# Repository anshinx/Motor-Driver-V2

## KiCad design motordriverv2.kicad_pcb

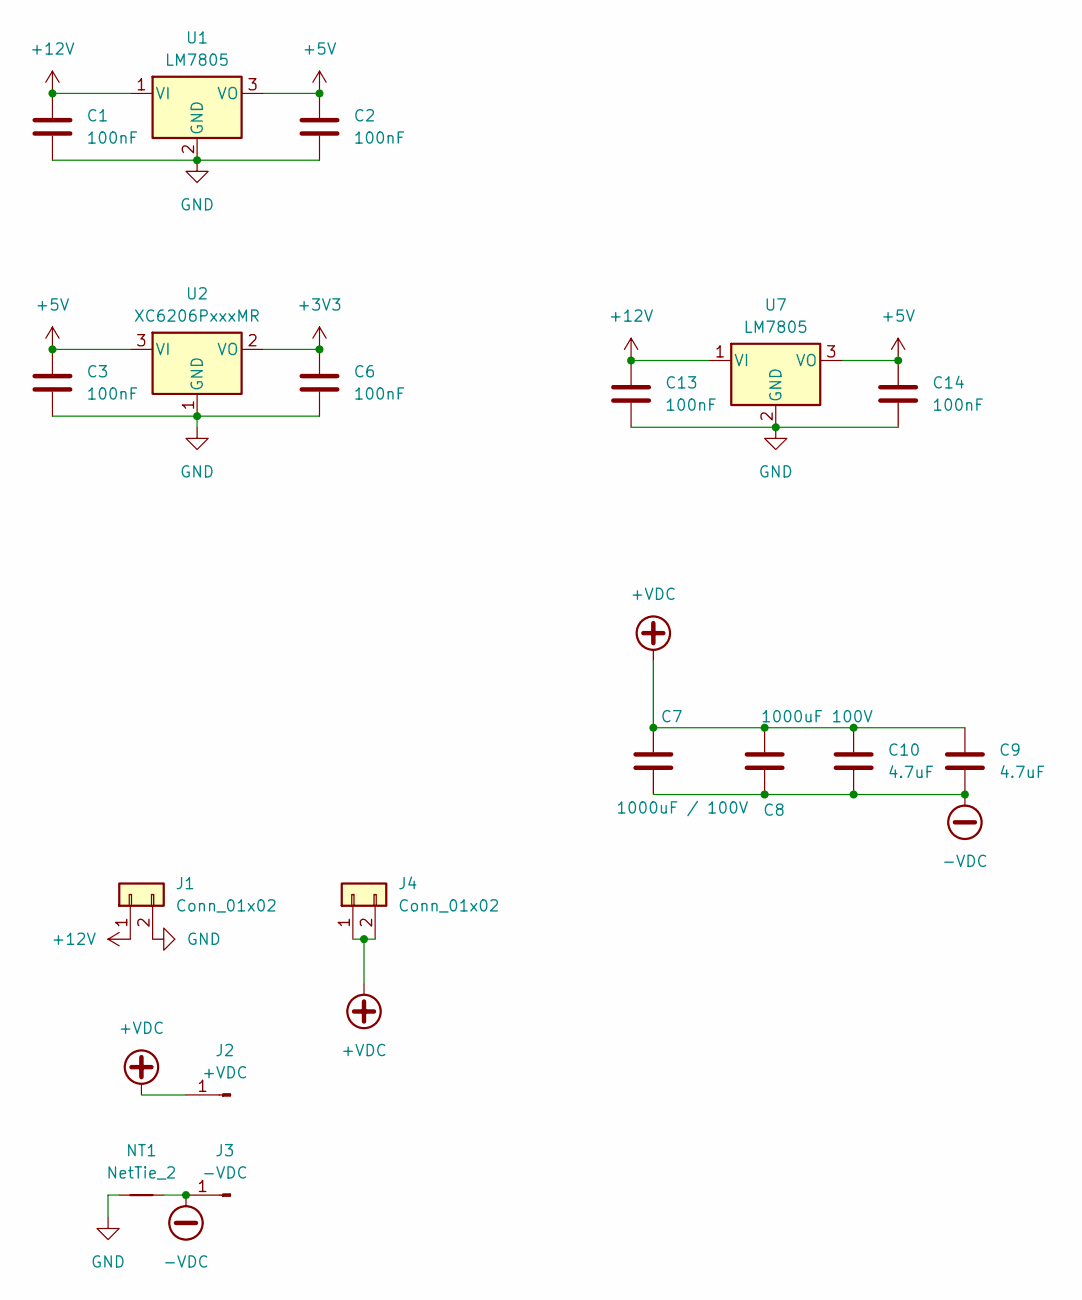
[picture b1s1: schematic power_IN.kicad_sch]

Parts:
C1, C2, C3, C6, C13, C14: 100nF; C_1210_3225Metric_Pad1.33x2.70mm_HandSolder
C7: 1000uF / 100V; CP_Radial_D18.0mm_P7.50mm
C8: 1000uF 100V; CP_Radial_D18.0mm_P7.50mm
C9, C10: 4.7uF; C_1210_3225Metric_Pad1.33x2.70mm_HandSolder
J1, J4: Conn_01x02; TerminalBlock_RND_205-00001_1x02_P5.00mm_Horizontal
J2: +VDC; SolderWirePad_1x01_SMD_5x10mm
J3: -VDC; SolderWirePad_1x01_SMD_5x10mm
NT1: NetTie_2; NetTie-2_SMD_Pad2.0mm
U1, U7: LM7805; TO-220-3_Vertical
U2: XC6206PxxxMR; SOT-23-3

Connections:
+3V3: C6.1, U2.2 (VO); also elsewhere on the board
+5V: C2.1, C3.1, C14.1, U1.3 (VO), U2.3 (VI), U7.3 (VO); also elsewhere on the board
+12V: C1.1, C13.1, J1.1, U1.1 (VI), U7.1 (VI); also elsewhere on the board
+VDC: C7.1, C8.1, C9.1, C10.1, J2.1 (Pin_1_1), J4.1, J4.2; also elsewhere on the board
-VDC: C7.2, C8.2, C9.2, C10.2, J3.1 (Pin_1_1), NT1.2; also elsewhere on the board
GND: C1.2, C2.2, C3.2, C6.2, C13.2, C14.2, J1.2, NT1.1, U1.2 (GND), U2.1 (GND), U7.2 (GND); also elsewhere on the board

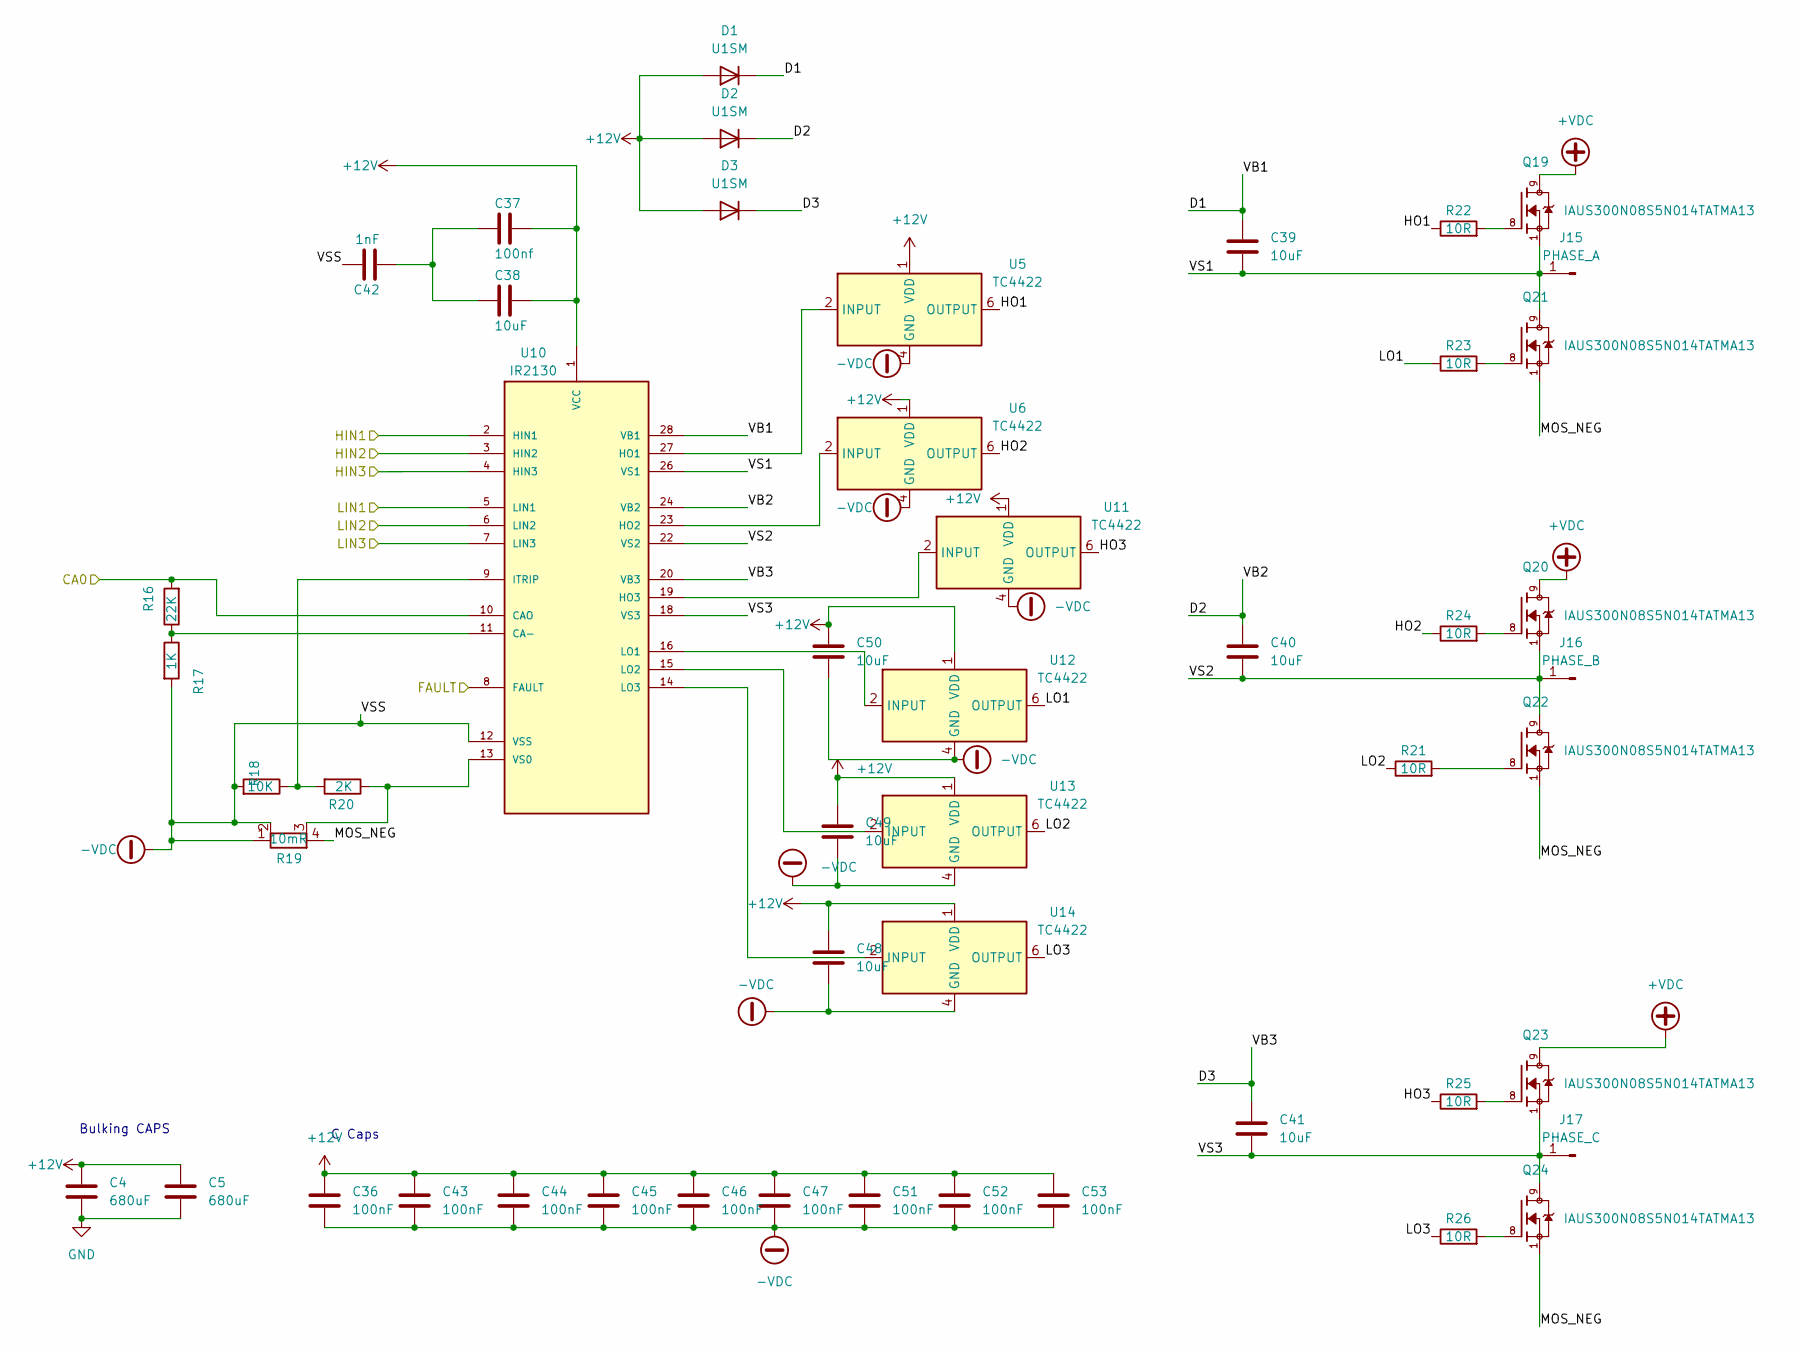
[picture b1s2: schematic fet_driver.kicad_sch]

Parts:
C4, C5: 680uF; CP_Radial_D10.0mm_P5.00mm
C36, C43, C44, C45, C46, C47, C51, C52, C53: 100nF; C_1210_3225Metric_Pad1.33x2.70mm_HandSolder
C37: 100nf; C_1210_3225Metric_Pad1.33x2.70mm_HandSolder
C38, C39, C40, C41, C48, C49, C50: 10uF; C_1210_3225Metric_Pad1.33x2.70mm_HandSolder
C42: 1nF; C_1210_3225Metric_Pad1.33x2.70mm_HandSolder
D1, D2, D3: U1SM; D_SMA_Handsoldering
J15: PHASE_A; SolderWirePad_1x01_SMD_5x10mm
J16: PHASE_B; SolderWirePad_1x01_SMD_5x10mm
J17: PHASE_C; SolderWirePad_1x01_SMD_5x10mm
Q19, Q20, Q21, Q22, Q23: IAUS300N08S5N014TATMA13; IAUS300N08S5N014TATMA1
Q24: IAUS300N08S5N014TATMA13; IAUS300N08S5N014TATMA
R16: 22K; R_1210_3225Metric
R17: 1K; R_1210_3225Metric
R18: 10K; R_1210_3225Metric
R19: 10mR; R_Shunt_Vishay_WSR2_WSR3_KelvinConnection
R20: 2K; R_1210_3225Metric
R21: 10R; R_1210_3225Metric_Pad1.30x2.65mm_HandSolder
R22, R23, R24, R25, R26: 10R; R_1210_3225Metric
U5, U6, U11, U12, U13, U14: TC4422; DIP-8_W7.62mm
U10: IR2130; DIP-28_W15.24mm; PARTREV P

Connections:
+12V: C4.1, C5.1, C36.1, C37.1, C38.1, C43.1, C44.1, C45.1, C46.1, C47.1, C48.1, C49.1, C50.1, C51.1, C52.1, C53.1, D1.2 (A), D2.2 (A), D3.2 (A), U5.1 (VDD), U5.8 (VDD), U6.1 (VDD), U6.8 (VDD), U10.1 (VCC), U11.1 (VDD), U11.8 (VDD), U12.1 (VDD), U12.8 (VDD), U13.1 (VDD), U13.8 (VDD), U14.1 (VDD), U14.8 (VDD); also elsewhere on the board
+VDC: Q19.9, Q19.10, Q19.11, Q19.12, Q19.13, Q19.14, Q19.15, Q19.16, Q20.9, Q20.10, Q20.11, Q20.12, Q20.13, Q20.14, Q20.15, Q20.16, Q23.9, Q23.10, Q23.11, Q23.12, Q23.13, Q23.14, Q23.15, Q23.16; also elsewhere on the board
-VDC: C36.2, C42.1, C43.2, C44.2, C45.2, C46.2, C47.2, C48.2, C49.2, C50.2, C51.2, C52.2, C53.2, R17.2, R18.2, R19.1, R19.2, U5.4 (GND), U5.5 (GND), U6.4 (GND), U6.5 (GND), U10.12 (VSS), U11.4 (GND), U11.5 (GND), U12.4 (GND), U12.5 (GND), U13.4 (GND), U13.5 (GND), U14.4 (GND), U14.5 (GND); also elsewhere on the board
/FET_DRIVER/CA0: R16.2, U10.10 (CAO); also elsewhere on the board
/FET_DRIVER/D1: C39.1, D1.1 (K), U10.28 (VB1)
/FET_DRIVER/D2: C40.1, D2.1 (K), U10.24 (VB2)
/FET_DRIVER/D3: C41.1, D3.1 (K), U10.20 (VB3)
/FET_DRIVER/FAULT: U10.8 (FAULT); also elsewhere on the board
/FET_DRIVER/HIN1: U10.2 (HIN1); also elsewhere on the board
/FET_DRIVER/HIN2: U10.3 (HIN2); also elsewhere on the board
/FET_DRIVER/HIN3: U10.4 (HIN3); also elsewhere on the board
/FET_DRIVER/HO1: R22.1, U5.6 (OUTPUT), U5.7 (OUTPUT)
/FET_DRIVER/HO2: R24.1, U6.6 (OUTPUT), U6.7 (OUTPUT)
/FET_DRIVER/HO3: R25.1, U11.6 (OUTPUT), U11.7 (OUTPUT)
/FET_DRIVER/LIN1: U10.5 (LIN1); also elsewhere on the board
/FET_DRIVER/LIN2: U10.6 (LIN2); also elsewhere on the board
/FET_DRIVER/LIN3: U10.7 (LIN3); also elsewhere on the board
/FET_DRIVER/LO1: R23.1, U12.6 (OUTPUT), U12.7 (OUTPUT)
/FET_DRIVER/LO2: R21.1, U13.6 (OUTPUT), U13.7 (OUTPUT)
/FET_DRIVER/LO3: R26.1, U14.6 (OUTPUT), U14.7 (OUTPUT)
/FET_DRIVER/MOS_NEG: Q21.1, Q21.2, Q21.3, Q21.4, Q21.5, Q21.6, Q21.7, Q22.1, Q22.2, Q22.3, Q22.4, Q22.5, Q22.6, Q22.7, Q24.1, Q24.2, Q24.3, Q24.4, Q24.5, Q24.6, Q24.7, R19.4
/FET_DRIVER/VS1: C39.2, J15.1 (Pin_1_1), Q19.1, Q19.2, Q19.3, Q19.4, Q19.5, Q19.6, Q19.7, Q21.9, Q21.10, Q21.11, Q21.12, Q21.13, Q21.14, Q21.15, Q21.16, U10.26 (VS1)
/FET_DRIVER/VS2: C40.2, J16.1 (Pin_1_1), Q20.1, Q20.2, Q20.3, Q20.4, Q20.5, Q20.6, Q20.7, Q22.9, Q22.10, Q22.11, Q22.12, Q22.13, Q22.14, Q22.15, Q22.16, U10.22 (VS2)
/FET_DRIVER/VS3: C41.2, J17.1 (Pin_1_1), Q23.1, Q23.2, Q23.3, Q23.4, Q23.5, Q23.6, Q23.7, Q24.9, Q24.10, Q24.11, Q24.12, Q24.13, Q24.14, Q24.15, Q24.16, U10.18 (VS3)
GND: C4.2, C5.2; also elsewhere on the board
unnamed: C37.2, C38.2, C42.2
unnamed: Q19.8, R22.2
unnamed: Q20.8, R24.2
unnamed: Q21.8, R23.2
unnamed: Q22.8, R21.2
unnamed: Q23.8, R25.2
unnamed: Q24.8, R26.2
unnamed: R16.1, R17.1, U10.11 (CA-)
unnamed: U5.2 (INPUT), U10.27 (HO1)
unnamed: U6.2 (INPUT), U10.23 (HO2)
unnamed: U10.19 (HO3), U11.2 (INPUT)
unnamed: R18.1, R20.2, U10.9 (ITRIP)
unnamed: U10.16 (LO1), U12.2 (INPUT)
unnamed: U10.15 (LO2), U13.2 (INPUT)
unnamed: U10.14 (LO3), U14.2 (INPUT)
unnamed: R19.3, R20.1, U10.13 (VS0)

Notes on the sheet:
C Caps
Bulking CAPS

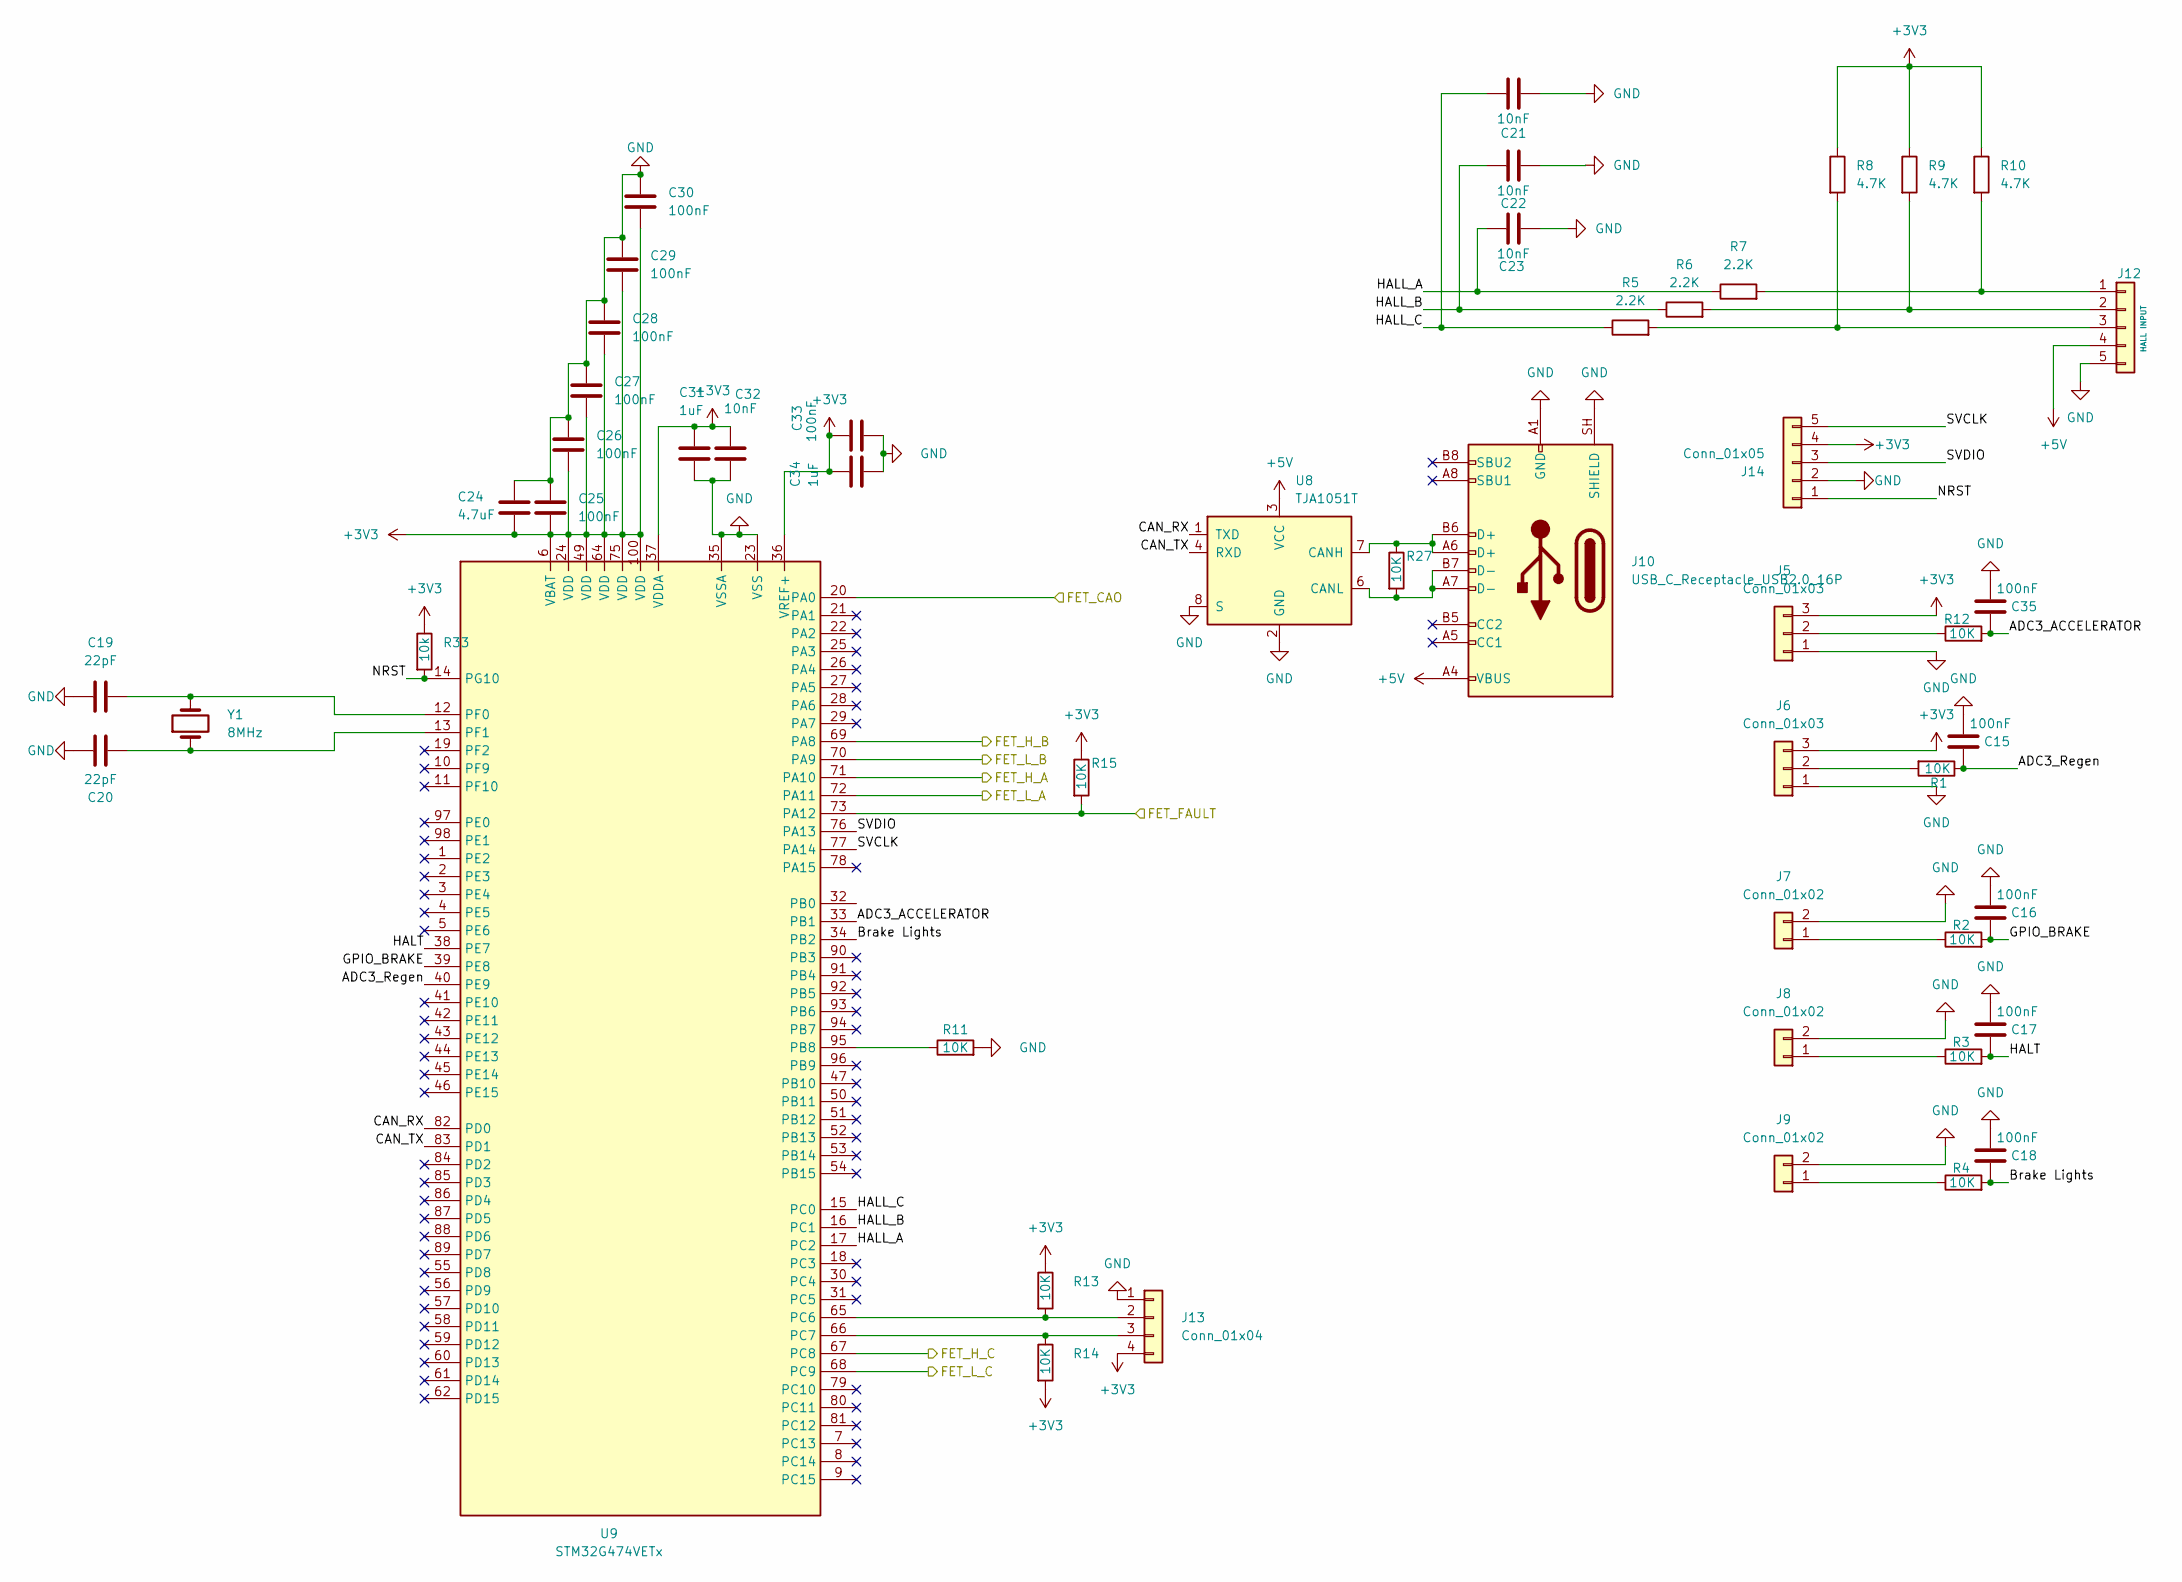
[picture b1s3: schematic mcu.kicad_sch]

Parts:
C15, C16, C17, C18, C25, C26, C27, C28, C29, C30, C33, C35: 100nF; C_0805_2012Metric_Pad1.18x1.45mm_HandSolder
C19, C20: 22pF; C_0603_1608Metric_Pad1.08x0.95mm_HandSolder
C21, C22, C23: 10nF; C_1210_3225Metric_Pad1.33x2.70mm_HandSolder
C24: 4.7uF; C_1210_3225Metric_Pad1.33x2.70mm_HandSolder
C31, C34: 1uF; C_0805_2012Metric_Pad1.18x1.45mm_HandSolder
C32: 10nF; C_0805_2012Metric_Pad1.18x1.45mm_HandSolder
J5, J6: Conn_01x03; TerminalBlock_RND_205-00002_1x03_P5.00mm_Horizontal
J7, J8, J9: Conn_01x02; TerminalBlock_RND_205-00001_1x02_P5.00mm_Horizontal
J10: USB_C_Receptacle_USB2.0_16P; USB_C_Receptacle_GCT_USB4105-xx-A_16P_TopMnt_Horizontal
J12: HALL INPUT; PinSocket_1x05_P2.00mm_Vertical
J13: Conn_01x04; PinHeader_1x04_P2.54mm_Vertical
J14: Conn_01x05; PinSocket_1x05_P2.54mm_Vertical
R1, R2, R3, R4, R11, R12, R13, R14, R15, R27: 10K; R_0805_2012Metric_Pad1.20x1.40mm_HandSolder
R5, R6, R7: 2.2K; R_1210_3225Metric
R8, R9, R10: 4.7K; R_1210_3225Metric
R33: 10k; R_0805_2012Metric_Pad1.20x1.40mm_HandSolder
U8: TJA1051T; SOIC-8_3.9x4.9mm_P1.27mm
U9: STM32G474VETx; LQFP-100_14x14mm_P0.5mm
Y1: 8MHz; Crystal_HC18-U_Vertical

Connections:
+3V3: C24.1, C25.2, C26.2, C27.2, C28.2, C29.2, C30.2, C31.2, C32.2, C33.2, C34.2, J5.3, J6.3, J13.4, J14.4, R8.1, R9.1, R10.1, R13.1, R14.2, R15.1, R33.1, U9.6 (VBAT), U9.24 (VDD), U9.36 (VREF+), U9.37 (VDDA), U9.49 (VDD), U9.64 (VDD), U9.75 (VDD), U9.100 (VDD); also elsewhere on the board
+5V: J10.A4 (VBUS), J10.A9 (VBUS), J10.B4 (VBUS), J10.B9 (VBUS), J12.4, U8.3 (VCC); also elsewhere on the board
/FET_DRIVER/CA0: U9.20 (PA0); also elsewhere on the board
/FET_DRIVER/FAULT: R15.2, U9.73 (PA12); also elsewhere on the board
/FET_DRIVER/HIN1: U9.71 (PA10); also elsewhere on the board
/FET_DRIVER/HIN2: U9.69 (PA8); also elsewhere on the board
/FET_DRIVER/HIN3: U9.67 (PC8); also elsewhere on the board
/FET_DRIVER/LIN1: U9.72 (PA11); also elsewhere on the board
/FET_DRIVER/LIN2: U9.70 (PA9); also elsewhere on the board
/FET_DRIVER/LIN3: U9.68 (PC9); also elsewhere on the board
/mcu/ADC3_ACCELERATOR: C35.2, R12.2, U9.33 (PB1)
/mcu/ADC3_Regen: C15.2, R1.1, U9.40 (PE9)
/mcu/Brake Lights: C18.2, R4.2, U9.34 (PB2)
/mcu/CAN_RX: U8.1 (TXD), U9.82 (PD0)
/mcu/CAN_TX: U8.4 (RXD), U9.83 (PD1)
/mcu/GPIO_BRAKE: C16.2, R2.2, U9.39 (PE8)
/mcu/HALL_A: C23.1, R7.1, U9.17 (PC2)
/mcu/HALL_B: C22.1, R6.1, U9.16 (PC1)
/mcu/HALL_C: C21.1, R5.1, U9.15 (PC0)
/mcu/HALT: C17.2, R3.2, U9.38 (PE7)
/mcu/NRST: J14.1, R33.2, U9.14 (PG10)
/mcu/SVCLK: J14.5, U9.77 (PA14)
/mcu/SVDIO: J14.3, U9.76 (PA13)
GND: C15.1, C16.1, C17.1, C18.1, C19.1, C20.1, C21.2, C22.2, C23.2, C24.2, C25.1, C26.1, C27.1, C28.1, C29.1, C30.1, C31.1, C32.1, C33.1, C34.1, C35.1, J5.1, J6.1, J7.2, J8.2, J9.2, J10.A1 (GND), J10.A12 (GND), J10.B1 (GND), J10.B12 (GND), J10.SH (SHIELD), J12.5, J13.1, J14.2, R11.2, U8.2 (GND), U8.8 (S), U9.23 (VSS), U9.35 (VSSA), U9.48 (VSS), U9.63 (VSS), U9.74 (VSS), U9.99 (VSS); also elsewhere on the board
unnamed: J5.2, R12.1
unnamed: J6.2, R1.2
unnamed: J7.1, R2.1
unnamed: J8.1, R3.1
unnamed: J9.1, R4.1
unnamed: J12.1, R7.2, R10.2
unnamed: J12.2, R6.2, R9.2
unnamed: J12.3, R5.2, R8.2
unnamed: J13.2, R13.2, U9.65 (PC6)
unnamed: J13.3, R14.1, U9.66 (PC7)
unnamed: J10.A6 (D+), J10.B6 (D+), R27.1, U8.7 (CANH)
unnamed: J10.A7 (D-), J10.B7 (D-), R27.2, U8.6 (CANL)
unnamed: R11.1, U9.95 (PB8)
unnamed: C19.2, U9.12 (PF0), Y1.2
unnamed: C20.2, U9.13 (PF1), Y1.1

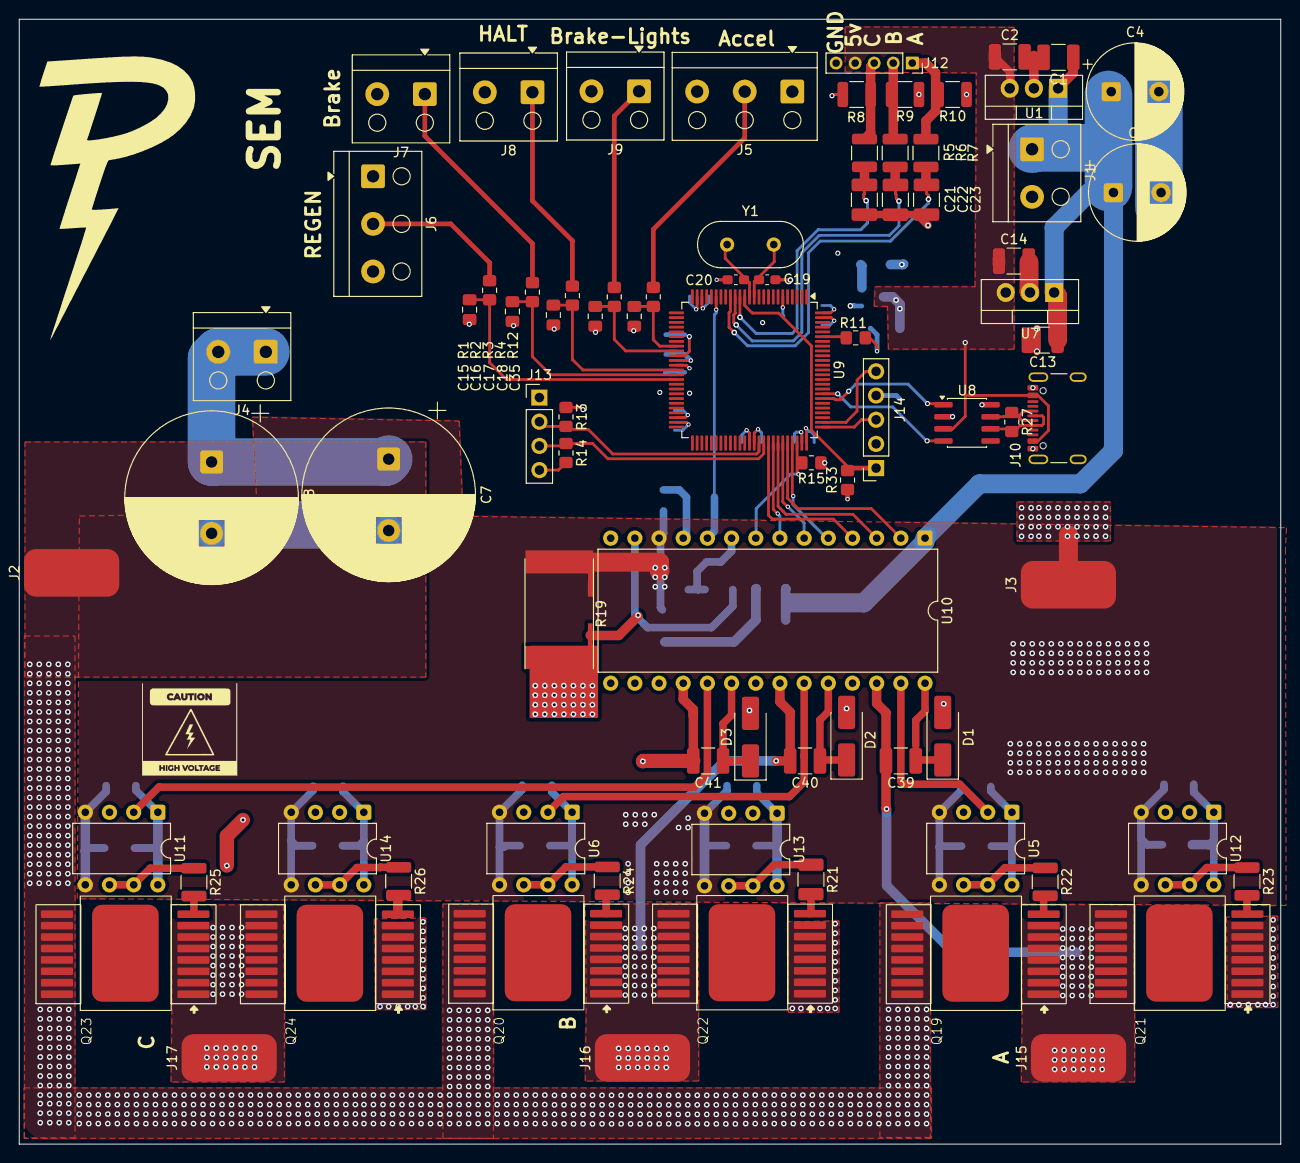
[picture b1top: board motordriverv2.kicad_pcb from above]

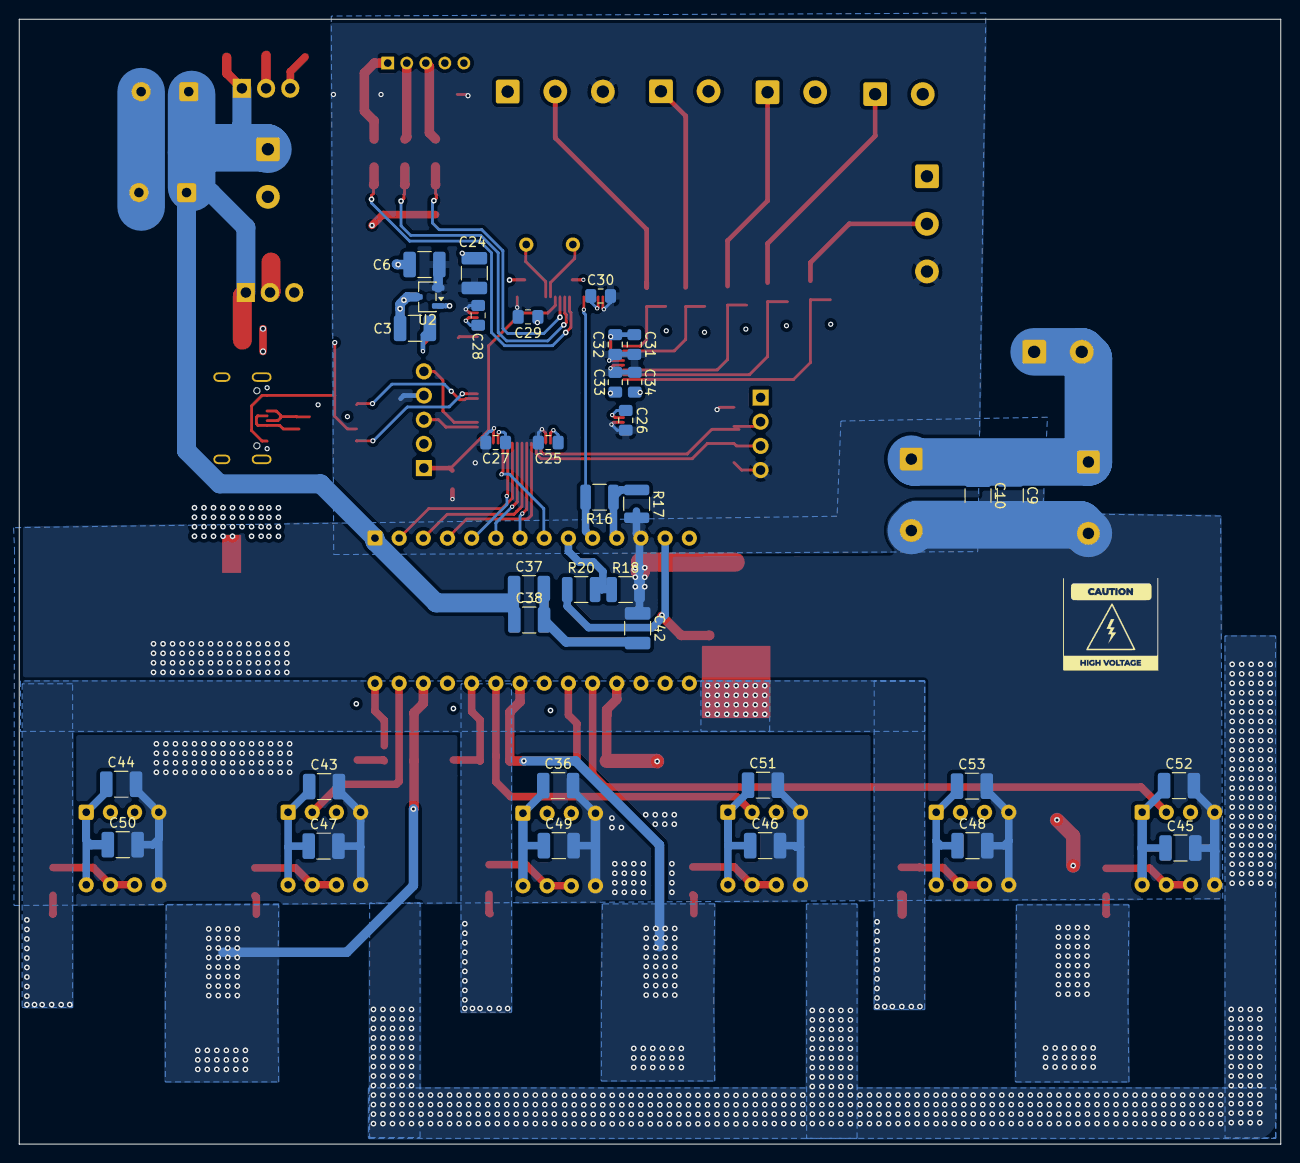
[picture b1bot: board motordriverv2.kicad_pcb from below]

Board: 4 copper layers, 132.5 x 118.2 mm, 118 parts (35 on the bottom side), 71 nets.

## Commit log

2026-05-07 fet tamam
2026-05-11 pcb geçiş
2026-05-11 pcb geçiş v2
